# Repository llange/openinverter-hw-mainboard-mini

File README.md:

Shield: [![CC BY-SA 4.0][cc-by-sa-shield]][cc-by-sa]

This work is licensed under a
[Creative Commons Attribution-ShareAlike 4.0 International License][cc-by-sa].

[![CC BY-SA 4.0][cc-by-sa-image]][cc-by-sa]

[cc-by-sa]: http://creativecommons.org/licenses/by-sa/4.0/
[cc-by-sa-image]: https://licensebuttons.net/l/by-sa/4.0/88x31.png
[cc-by-sa-shield]: https://img.shields.io/badge/License-CC%20BY--SA%204.0-lightgrey.svg

inverter-hardware (mainboard mini)
==================================
**KiCad** schematics and board for J. Huebner and openinverter.org inverter - main board mini version.

# Table of Contents
<details>
 <summary>Click to open TOC</summary>
<!-- MarkdownTOC autolink="true" levels="1,2,3,4,5,6" bracket="round" style="unordered" indent="    " autoanchor="false" markdown_preview="github" -->

- [About](#about)
    - [Changes brought by this repository](#changes-brought-by-this-repository)
- [Ecosystem](#ecosystem)
    - [Hardware](#hardware)
    - [Firmware](#firmware)
- [Regarding this board](#regarding-this-board)
    - [Usual disclaimer](#usual-disclaimer)
    - [Setup](#setup)
    - [Design](#design)
    - [Custom fields for Manufacturer Part Numbers](#custom-fields-for-manufacturer-part-numbers)
    - [Fabrication](#fabrication)

<!-- /MarkdownTOC -->
</details>

# About
This repository, "**openinverter-hw-mainboard-mini**", hosts the KiCad schematics for OpenInverter.org "mainboard mini" inverter.

It's a derivative of [inverter hardware](https://github.com/jsphuebner/inverter-hardware) by J. Huebner and openinverter.org used under [CC BY-SA 4.0](https://creativecommons.org/licenses/by-sa/4.0)

[**openinverter-hw-mainboard-mini**](https://github.com/llange/openinverter-hw-mainboard-mini) &copy; 2022 by [llange](https://github.com/llange) is licensed under [CC BY-SA 4.0](https://creativecommons.org/licenses/by-sa/4.0)

It is an [Open Source Hardware](https://www.oshwa.org/definition/) project: _"Open source hardware is hardware whose design is made publicly available so that anyone can study, modify, distribute, make, and sell the design or hardware based on that design. The hardware’s source, the design from which it is made, is available in the preferred format for making modifications to it."_

As such, we publish:
* the original schematic and board layout files - to allow people modify the hardware
* alternative or intermediate formats that can be viewed or edited ([PDFs of circuit schematics](documentation/mainboard-mini\ schematic.pdf), [Gerbers for circuit board layouts](production/), ...) - to allow people to study or make some use of the design without having to use KiCad for that.

## Changes brought by this repository
According to the terms of the license, we notify you that this [**openinverter-hw-mainboard-mini**](https://github.com/llange/openinverter-hw-mainboard-mini) is a modification of the original [inverter hardware mainboard mini (schematics)](https://github.com/jsphuebner/inverter-hardware/blob/master/mainboard-mini.sch) and [inverter hardware mainboard mini (board)](https://github.com/jsphuebner/inverter-hardware/blob/master/mainboard-mini.brd) with the following changes:
* Conversion (from Eagle) to [KiCad 6.0](https://www.kicad.org/)
* Change of parts symbols and footprints to better integrate in KiCad ecosystem (esp. 3D rendering)
* Many errors have certainly been introduced in the process !!

# Ecosystem

This hardware is part of a broad ecosystem and community (OpenInverter) of enthusiasts that aims to democratize the EV conversion landscape, by researching and sharing knowledge ; and creating hardware (such as this one) to help buildings EV.

You can find more informations here:
* [OpenInverter Web site](https://openinverter.org/)
* [OpenInverter Forum](https://openinverter.org/forum/)
* [OpenInverter Wiki](https://openinverter.org/wiki/)
* [EVBMW](https://www.evbmw.com/)

Main contributors
* [Johannes Huebner](https://github.com/jsphuebner/)
* [Damien Maguire](https://github.com/damienmaguire/)
* ...and a lot of others that I forgot to put here - sorry!

## Hardware

You can buy original boards (not this one but the [original Eagle board](https://github.com/jsphuebner/inverter-hardware/blob/master/mainboard-mini.brd)):
* [OpenInverter shop - mainoard mini - community edition](https://openinverter.org/shop/index.php?route=product/product&path=59&product_id=70)
* [OpenInverter shop - BMW i3™ inverter drop-in board - community edition](https://openinverter.org/shop/index.php?route=product/product&path=59&product_id=72)
* [OpenInverter shop - Nissan Leaf™ Gen 2 controller - community edition](https://openinverter.org/shop/index.php?route=product/product&path=59&product_id=57)
* [OpenInverter shop - Nissan Leaf™ Gen 2 controller - with personal support](https://openinverter.org/shop/index.php?route=product/product&path=59&product_id=53)

## Firmware
You can find the firmware for this board [here](https://github.com/jsphuebner/stm32-sine).

# Regarding this board

## Usual disclaimer
All files are provided as-is. Physical realization of any circuit requires design review and appropriate selection of components.  

The information provided in this repository is intended as information only. The Open Inverter project and it's contributors take no responsibility for how you use the information contained within these pages, nor any liability for damage, harm, injuries, or death, that may result from your actions.  

You undertake **your** project at **your own risk**. 

## Setup
_Please note : I (llange) don't design circuits for a living, and am by no means a KiCad expert. All design issues you'll find in this repository have certainly been accidentally intoduced by me at some point. Don't use this repository without your own judgment and experience._  

To properly use this repository you will need:
* A working [KiCad installation (>= 6.x)](https://www.kicad.org/)
* The [Fabrication Toolkit for KiCad](https://github.com/bennymeg/JLC-Plugin-for-KiCad) (JLC PCB Plug-in for KiCad) if you want to order make your boards with JLCPCB

Of course there are other possible plugins to enable you to automate the making of your boards with other providers, here are some examples among the many available:
* [PCBWay Plug-in for Kicad](https://github.com/pcbway/PCBWay-Plug-in-for-Kicad)
* [NextPCB Plug-in for Kicad](https://gitlab.com/nextpcbofficial/NextPCB-Plug-in-for-Kicad/)
* [AISLER Push for KiCad](https://github.com/AislerHQ/PushForKiCad)
* [kicad-gerberzipper](https://github.com/g200kg/kicad-gerberzipper)
* [KiKit – Automation for KiCAD](https://github.com/yaqwsx/KiKit)
* etc ...

## Design
* I try to have all ERC / DRC warnings and errors removed.
* In the future I'll try to add specific constraints for manufacturers (don't know yet what is possible with kicad_dru files)

## Custom fields for Manufacturer Part Numbers

You'll find that all these plugins expect some kind of "Part Number" reference field for each component:
* For AISLER plugin it's one of ['mpn', 'MPN', 'Mpn', 'AISLER_MPN'](https://github.com/AislerHQ/PushForKiCad/blob/2b171c85127c3b3b01a7c3be513bdc8cd8693f6d/src/push_thread.py#L171)
* For JLCPCB plugin it's one of ['mpn', 'Mpn', 'MPN', 'JLC_MPN', 'LCSC_MPN', 'LCSC Part #', 'JLC', 'LCSC'](https://github.com/bennymeg/JLC-Plugin-for-KiCad/blob/a39b65c94c322160cc0accf409dcafcb7271a910/plugins/process.py#L186)
* For PCBWay plugin it's one of ['mpn', 'MPN', 'Mpn', 'PCBWay_MPN'](https://github.com/pcbway/PCBWay-Plug-in-for-Kicad/blob/4dc1a54cb858d88d19062207046e60a83a8cbea9/plugins/thread.py#L151)
* For NextPCB plugin it's one of ['mpn', 'MPN', 'Mpn', 'NextPCB_MPN'](https://gitlab.com/nextpcbofficial/NextPCB-Plug-in-for-Kicad/-/blob/0c57b36d220ea69d5c8d31feb5939e7f558bd829/plugins/thread.py#L151)
* etc...

I'd recommend to use the most specific one ; i.e. do **not** use the fields ['mpn', 'MPN', 'Mpn'] as it's likely that the part number will be very different from one provider to the other, and we want to let the end-user choose his own manufacturer.

For JLC PCB I used the **JLC** field name. You're welcome to use **AISLER_MPN**, **PCBWay_MPN** and **NextPCB_MPN** if you use those providers, etc... 

## Fabrication
(This has not been tested yet. Please review all files / component selection before doing any fabrication process)
In theory:
* In KiCad, produce manufacturing file by clicking on the "Fabrication Toolkit" icon
* A folder (`production`) will open with some files:
  * gerber.zip : a zip containing all the 4 files below, plus the gerber files (copper traces, drilling instructions, ...) 
  * bom.csv : The Bill Of Materials - needed for purchasing parts
  * designators.csv : ?
  * netlist.ipc : IPC netlist file
  * positions.csv : Pick and Place file
* Upload this file to JLCPCB and follow the process

_(To be continued...)_

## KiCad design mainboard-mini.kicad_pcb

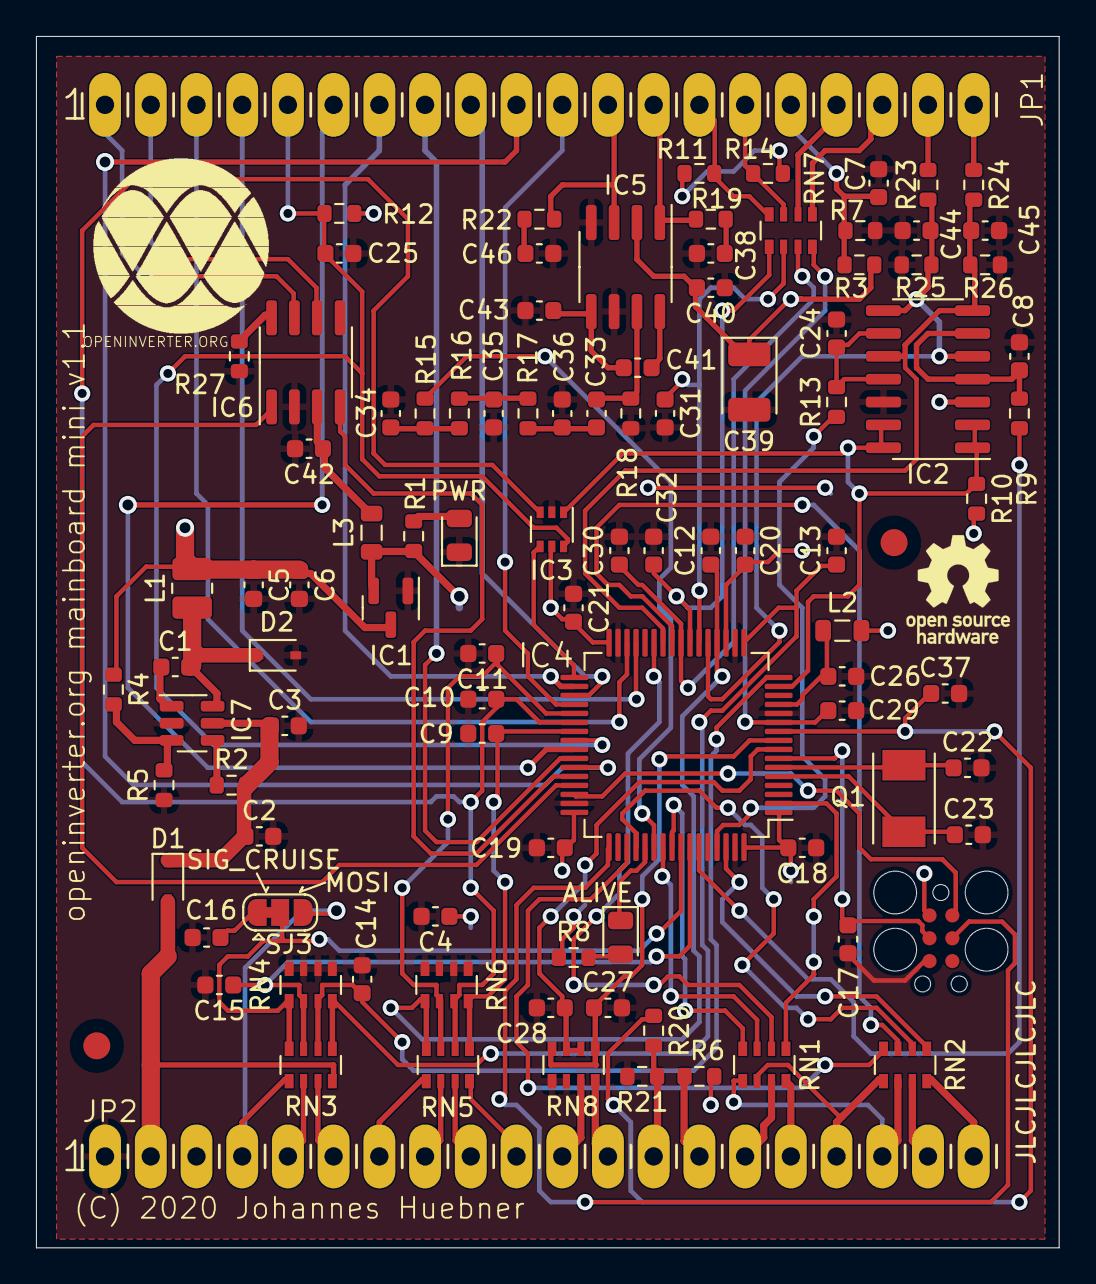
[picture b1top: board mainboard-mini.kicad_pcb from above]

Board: 2 copper layers, 56.8 x 67.3 mm, 105 parts (1 on the bottom side), 101 nets.

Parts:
ALIVE0: LED_0603_GN; LED_0805_2012Metric
C1, C33, C34, C35, C36, C43: 22n; C_0603_1608Metric
C2, C4, C6, C7, C26, C41: 10µ; C_0603_1608Metric
C3, C5, C8, C9, C10, C11, C12, C13, C14, C15, C16, C17, C18, C19, C20, C21, C24, C27, C28, C29, C30, C37, C40, C42: 1µ; C_0603_1608Metric
C22, C23: 20p; C_0603_1608Metric
C25, C31, C32, C44, C45: 1nF; C_0603_1608Metric
C38, C46: 100n; C_0603_1608Metric
C39: 100µ; CP_EIA-3528-21_Kemet-B
D1, D2: 1N5819WS; D_SOD-323
FID1, FID2: Fiducial_1.5mm_Mask3mm
IC1: XC6206P332MR; SOT-23
IC2: LM2901; SOIC-14_3.9x8.7mm_P1.27mm
IC3: NC7SZ10P6X; SOT-363_SC-70-6
IC4: STM32F103RBT6; LQFP-64_10x10mm_P0.5mm
IC5: TDA2822D; SOIC-8_3.9x4.9mm_P1.27mm
IC6: SN65HVD230; SOIC-8_3.9x4.9mm_P1.27mm
IC7: RT8259GE; SOT-23-6
J1: TC2030_SWD-MCP; TC2030-MCP
JP1, JP2: PINHD-1X20; 1X20
L1: 4.7µH; L_1008_2520Metric
L2: 100µH; L_0805_2012Metric
L3: 10µH; L_0805_2012Metric
LOGO1: OSHW-LOGOM; OSHW-Logo_5.7x6mm_SilkScreen
PWR0: LED_0603_GN; LED_0805_2012Metric
Q1: 8MHz; Crystal_SMD_TXC_7A-2Pin_5x3.2mm
R1, R3, R6, R8, R11, R14, R21: 510; R_0603_1608Metric
R2: 100k; R_0603_1608Metric
R4: 51k; R_0603_1608Metric
R5, R9, R10, R12, R13, R15, R18, R20, R27: 10k; R_0603_1608Metric
R7: 220; R_0603_1608Metric
R16, R17, R23, R24: 3k3; R_0603_1608Metric
R19, R22: 4R7; R_0603_1608Metric
R25, R26: 6k8; R_0603_1608Metric
RN1, RN2: 470; R_Array_Convex_4x0603
RN3, RN5: 4k7; R_Array_Convex_4x0603
RN4, RN6: 1k2; R_Array_Convex_4x0603
RN7, RN8: 10k; R_Array_Convex_4x0603
SJ1: SOLDERJUMPERNO; SolderJumper-2_P1.3mm_Open_RoundedPad1.0x1.5mm
SJ3: SOLDERJUMPER_2WAYPASTE2&3; SolderJumper-3_P1.3mm_Bridged12_RoundedPad1.0x1.5mm
U$2: OI_LOGO

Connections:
+12V: D1.2 (A), JP2.2, RN3.4 (R4.1)
/CANH: IC6.7 (CANH), JP1.1
/CANL: IC6.6 (CANL), JP1.2
/ENC_A/S2: JP1.14, R11.2, RN7.8 (R1.2)
/ENC_B/S3: JP1.15, R14.2, RN7.7 (R2.2)
/I_L1: JP1.19, R23.1
/I_L2: JP1.20, R24.1
/MTEMP+: JP2.14, R6.1
/MTEMP-: JP2.13, R20.2, R21.1
/NRST: C17.1, IC4.7 (NRST), J1.3 (~RESET)
/OUT_BRAKE: JP2.18, RN1.5 (R4.2), RN2.6 (R3.2)
/OUT_DCSW: JP2.16, RN1.8 (R1.2)
/OUT_ERR: JP2.17, RN1.6 (R3.2), RN2.5 (R4.2)
/OUT_OUVTG: JP2.19, RN2.7 (R2.2)
/OUT_PRE: JP2.15, RN1.7 (R2.2)
/PA1/TIM2_CH2: IC2.1, IC2.2, IC2.13, IC2.14, IC3.1 (I0), IC4.15 (PA1), R10.1
/PA2/ADC2: C14.1, IC4.16 (PA2), RN3.6 (R3.2), RN4.3 (R3.1)
/PA3/ADC3: C13.1, IC4.17 (PA3), RN3.5 (R4.2), RN4.4 (R4.1)
/PA4/ADC4: C12.1, IC4.20 (PA4), RN5.4 (R4.1), RN6.5 (R4.2)
/PA5/ADC5: C44.1, IC2.5 (+), IC2.8 (-), IC4.21 (PA5), R23.2, R25.2
/PA6/TIM3_CH1: C31.1, IC4.22 (PA6), RN7.2 (R2.1)
/PA7/TIM3_CH2: C32.1, IC4.23 (PA7), RN7.1 (R1.1)
/PA8/TIM1_CH1: IC4.41 (PA8), JP1.6
/PA9/TIM1_CH2: IC4.42 (PA9), JP1.8
/PA10/TIM1_CH3: IC4.43 (PA10), JP1.10
/PA11/CANRX: IC4.44 (PA11), IC6.4 (R)
/PA12/CANTX: IC4.45 (PA12), IC6.1 (D)
/PB0/ADC8: C45.1, IC2.7 (+), IC2.10 (-), IC4.26 (PB0), R24.2, R26.2
/PB1/ADC9: IC4.27 (PB1), RN1.2 (R2.1)
/PB3/SPI1_SCK: IC4.55 (PB3), RN1.3 (R3.1)
/PB4/SPI1_MISO: IC4.56 (PB4), RN1.4 (R4.1)
/PB5/SPI1_MOSI: IC4.57 (PB5), RN3.8 (R1.2), RN4.1 (R1.1), SJ3.2 (C)
/PB6/TIM4_CH1: C15.1, IC4.58 (PB6), RN3.7 (R2.2), RN4.2 (R2.1)
/PB7/TIM4_CH2: IC4.59 (PB7), R9.1
/PB8/TIM4_CH3: IC4.61 (PB8), R13.1
/PB9/TIM4_CH4: IC4.62 (PB9), RN2.1 (R1.1)
/PB10/USART3_TX: IC4.29 (PB10), JP1.4
/PB11/USART3_RX: IC4.30 (PB11), JP1.3
/PB12/TIM1_BKIN: IC3.4 (O), IC4.33 (PB12)
/PC0/ADC10: C28.1, IC4.8 (PC0), RN8.2 (R2.1), RN8.3 (R3.1)
/PC1/ADC11: C27.1, IC4.9 (PC1), RN8.1 (R1.1), RN8.4 (R4.1)
/PC2/ADC12: C37.1, IC4.10 (PC2), R20.1
/PC3/ADC13: C29.1, IC4.11 (PC3), RN7.4 (R4.1)
/PC4/ADC14: C30.1, IC4.24 (PC4), RN7.3 (R3.1)
/PC5/ADC15: IC4.25 (PC5), RN2.3 (R3.1)
/PC6: C11.1, IC4.37 (PC6), RN5.3 (R3.1), RN6.6 (R3.2)
/PC7: C10.1, IC3.3 (I1), IC4.38 (PC7), RN5.2 (R2.1), RN6.7 (R2.2)
/PC8: C9.1, IC4.39 (PC8), RN5.1 (R1.1), RN6.8 (R1.2)
/PC9: C25.1, IC3.6 (I2), IC4.40 (PC9), JP1.5, R12.1
/PC10: IC4.51 (PC10), RN2.4 (R4.1)
/PC11: IC4.52 (PC11), RN2.2 (R2.1)
/PC12: ALIVE0.1 (K), IC4.53 (PC12)
/PC13: IC4.2 (PC13), RN1.1 (R1.1)
/PD2/TIM3_ETR: IC4.54 (PD2), R15.1
/PWM_USER: JP2.20, RN2.8 (R1.2)
/R1: IC5.1 (OUT), JP1.13, R19.2
/R2: IC5.3 (OUT), JP1.12, R22.2
/RES_BIAS: C7.1, JP1.16, R3.1, R7.2
/SIG_BMS: JP2.10, RN5.8 (R1.2)
/SIG_BRAKE: JP2.6, RN3.3 (R3.1)
/SIG_CRUISE: JP2.4, RN3.1 (R1.1), SJ3.3 (B)
/SIG_EMCYSTOP: JP2.9, RN5.7 (R2.2)
/SIG_FORWARD: JP2.7, RN5.5 (R4.2)
/SIG_REVERSE: JP2.8, RN5.6 (R3.2)
/SIG_START: JP2.5, RN3.2 (R2.1)
/THROTTLE1: JP2.12, RN8.8 (R1.2)
/THROTTLE2: JP2.11, RN8.7 (R2.2)
/TIM1_CH1N: IC4.34 (PB13), JP1.7
/TIM1_CH2N: IC4.35 (PB14), JP1.9
/TIM1_CH3N: IC4.36 (PB15), JP1.11
/TMPHS: JP1.17, RN7.6 (R3.2)
/UDC: JP1.18, RN7.5 (R4.2)
GND: C2.2, C3.2, C4.2, C5.2, C6.2, C7.2, C8.2, C9.2, C10.2, C11.2, C12.2, C13.2, C14.2, C15.2, C16.1, C17.2, C18.1, C19.1, C20.1, C21.1, C22.2, C23.2, C24.2, C25.2, C26.1, C27.2, C28.2, C29.2, C30.2, C31.2, C32.2, C34.2, C35.2, C36.2, C37.2, C38.1, C39.2, C40.1, C42.2, C43.1, C44.2, C45.2, C46.2, D2.2 (A), IC1.1 (GND), IC2.12 (V-), IC3.2 (GND), IC4.12 (VSSA), IC4.18 (VSS_4), IC4.31 (VSS_1), IC4.47 (VSS_2), IC4.60 (BOOT0), IC4.63 (VSS_3), IC5.4 (V-), IC5.6 (+IN), IC6.2 (GND), IC7.2 (GND), J1.5 (GND), JP2.1, PWR0.1 (K), R5.1, R7.1, R18.1, R21.2, R25.1, R26.1, R27.2, RN4.5 (R4.2), RN4.6 (R3.2), RN4.7 (R2.2), RN4.8 (R1.2), RN6.1 (R1.1), RN6.2 (R2.1), RN6.3 (R3.1), RN6.4 (R4.1), RN8.5 (R4.2), RN8.6 (R3.2)
unnamed: ALIVE0.2 (A), R8.2
unnamed: C1.1, IC7.1 (BST)
unnamed: C1.2, D2.1 (C), IC7.6 (SW), L1.1
unnamed: C2.1, C3.1, D1.1 (C), IC7.5 (IN), R2.2
unnamed: C8.1, IC2.4 (-), IC2.6 (-), R9.2
unnamed: C16.2, SJ3.1 (A)
unnamed: C22.1, IC4.6 (PD1/OSC=>), Q1.1
unnamed: C23.1, IC4.5 (PD0/OSC<=), Q1.2
unnamed: C24.1, IC2.9 (+), IC2.11 (+), R13.2
unnamed: C26.2, IC4.13 (VDDA), L2.1
unnamed: C33.1, C36.1, R17.2
unnamed: C33.2, IC5.7 (+IN), R18.2
unnamed: C34.1, R15.2, R16.1
unnamed: C35.1, R16.2, R17.1
unnamed: C38.2, R19.1
unnamed: C41.1, C43.2, IC5.5 (-IN)
unnamed: C41.2, IC5.8 (-IN)
unnamed: C42.1, IC6.3 (VCC), L3.2
unnamed: C46.1, R22.1
unnamed: IC4.46 (PA13), J1.2 (SWDIO/TMS)
unnamed: IC4.49 (PA14), J1.4 (SWCLK/TCK)
unnamed: IC6.8 (Rs), R27.1
unnamed: IC7.3 (FB), R4.2, R5.2
unnamed: IC7.4 (EN), R2.1
unnamed: PWR0.2 (A), R1.2
unnamed: R11.1, R14.1, SJ1.1
VCC: C5.1, C6.1, C39.1, C40.2, IC1.3 (VI), IC2.3 (V+), IC5.2 (V+), JP2.3, L1.2, R3.2, R4.1, R6.2, R12.2, SJ1.2
VCCIO: C4.1, C18.2, C19.2, C20.2, C21.2, IC1.2 (VO), IC3.5 (VCC), IC4.1 (VBAT), IC4.19 (VDD_4), IC4.32 (VDD_1), IC4.48 (VDD_2), IC4.64 (VDD_3), J1.1 (VCC), L2.2, L3.1, R1.1, R8.1, R10.2

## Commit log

2022-07-22 Initial commit : LICENSE and README
2022-07-22 Converted board looking good
2022-07-22 Adding produced files (documentation / production)

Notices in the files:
mainboard-mini.kicad_pcb:
(C) 2020 Johannes Huebner
parts and their libraries:
©2009 ROFA.cz - modified and updated by Robert Darlington ‹rdarlington@gmail.com›
